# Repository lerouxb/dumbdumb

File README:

DumbDumb Terminal
===

A little smart hardware serial terminal for use with REPLs like MicroPython in the form of a Feather Wing.

Directory structure
---

### cpp

platform.io and arduino stm32-core based firmware for the stm32g071r8. Scans the keyboard matrix, handles the LCD. Reads and writes over serial. Understands a small subset of VT100 terminal functionality. Just enough to fully support MicroPython's readline REPL.

### node

Some node.js based code to parse, modify and format KiCAD's PCB file format which is some variant of LISP. Contains a script that uses all of that to modify a pcb file to layout the keyboard's buttons. A lot more convenient for making changes to the button positioning than moving each of them around manually in KiCAD's interface every time I want to make changes to the layout.

### pcb

KiCAD files for the PCB. Includes tons of custom symbols and parts.

### py

The dupterm code for the esp32 port of MicroPython to duplicate the REPL on UART 2 which is the one that's exposed by the Adafruit Huzzah32 Feather's RX and TX pins. ie. the ones that are connected to DumbDumb's STM32 microcontroller when you plug the Feather in.

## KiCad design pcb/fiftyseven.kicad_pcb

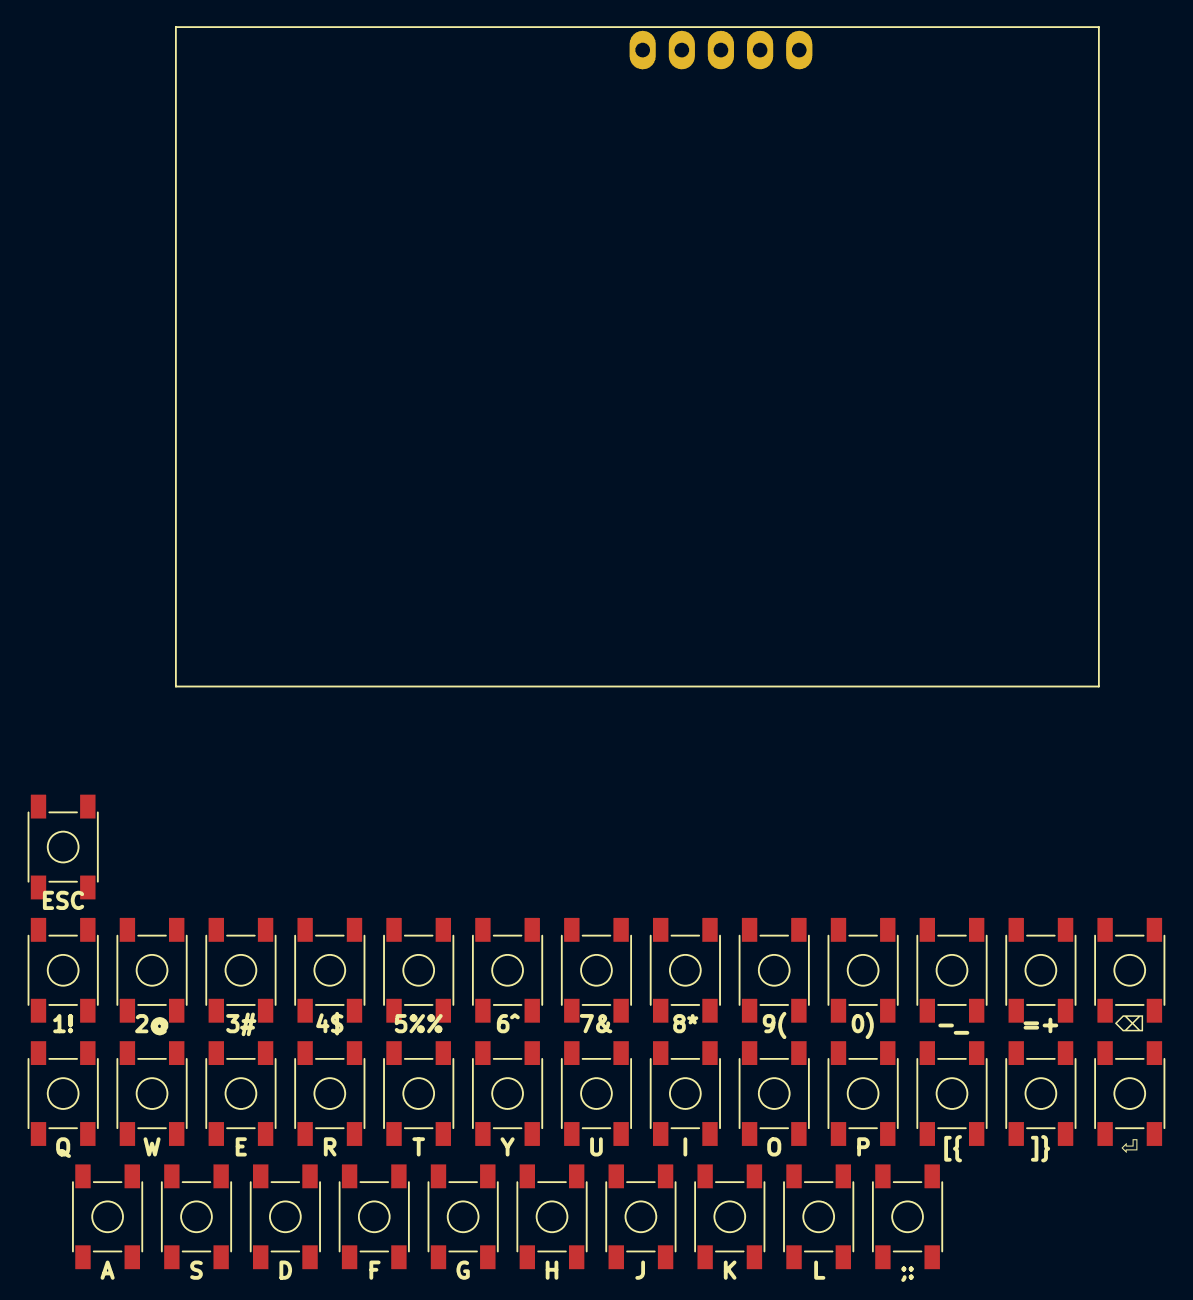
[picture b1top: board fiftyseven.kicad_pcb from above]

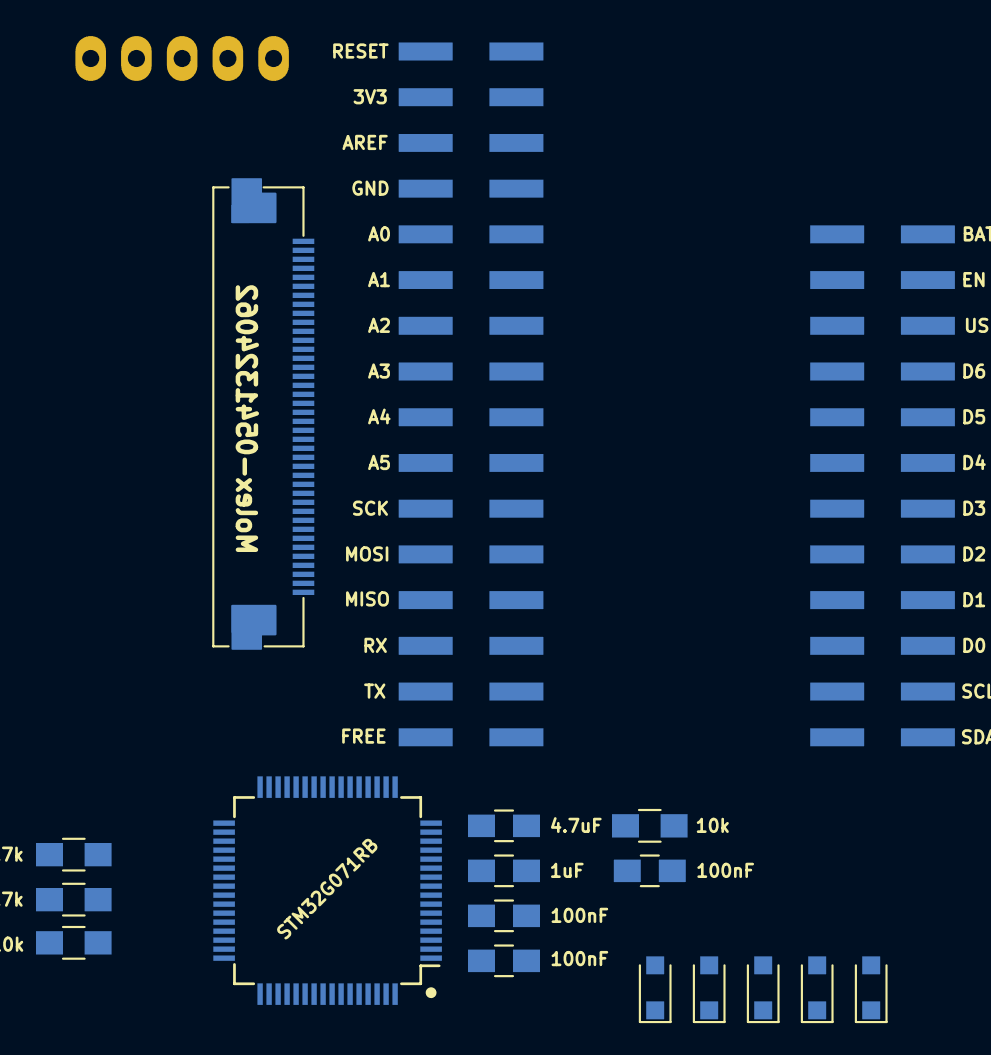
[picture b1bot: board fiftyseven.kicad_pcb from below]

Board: 2 copper layers, 56 parts (17 on the bottom side), 53 nets, no tracks yet.

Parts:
C10, C12, C17: 100nF; C_0805_HandSoldering
C11: 4.7uF; C_0805_HandSoldering
C13: 1uF; C_0805_HandSoldering
D1, D2, D3, D4, D5: D; D_SOD-323_HandSoldering
J1: Feather; FeatherHolderSMD
J2: STM32 SWD; SWD_Header
R1, R12: 10k; R_0805_HandSoldering
R10, R11: 4.7k; R_0805_HandSoldering
SW0:0, SW0:1, SW0:2, SW0:3, SW0:4, SW0:5, SW0:6, SW0:7, SW0:8, SW0:9, SW0:10, SW0:11, SW0:12, SW1:0, SW1:1, SW1:2, SW1:3, SW1:4, SW1:5, SW1:6, SW1:7, SW1:8, SW1:9, SW1:10, SW1:11, SW1:12, SW2:0, SW2:1, SW2:2, SW2:3, SW2:4, SW2:5, SW2:6, SW2:7, SW2:8, SW2:9, SW2:10: SW_Push; 4.5mm-switch
SW:ESC1: SW_Push; 4.5mm-switch
U1: STM32G071RB; STM32G0-LQFP-64
U6: 240x320_16bit; LCD-320x240

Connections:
+3V3: C10.1, C11.1, C12.1, C13.1, J1.14, J2.1, R1.1, R10.1, R11.1, SW:ESC1.1, U1.6, U1.7, U1.8
C0: SW0:0.2, SW1:0.2, SW2:0.2, U1.11
C1: SW0:1.2, SW1:1.2, SW2:1.2, U1.13
C2: SW0:2.2, SW1:2.2, SW2:2.2, U1.14
C3: SW0:3.2, SW1:3.2, SW2:3.2, U1.15
C4: SW0:4.2, SW1:4.2, SW2:4.2, U1.16
C5: SW0:5.2, SW1:5.2, SW2:5.2, U1.17
C6: SW0:6.2, SW1:6.2, SW2:6.2, U1.18
C7: SW0:7.2, SW1:7.2, SW2:7.2, U1.19
C8: SW0:8.2, SW1:8.2, SW2:8.2, U1.20
C9: SW0:9.2, SW1:9.2, SW2:9.2, U1.21
C10: SW0:10.2, SW1:10.2, U1.22
C11: SW0:11.2, SW1:11.2, U1.23
C12: SW0:12.2, SW1:12.2, U1.24
DB0: U1.27, U6.14
DB1: U1.28, U6.15
DB2: U1.29, U6.16
DB3: U1.57, U6.17
DB4: U1.58, U6.18
DB5: U1.59, U6.19
DB6: U1.60, U6.20
DB7: U1.61, U6.21
DB8: U1.62, U6.22
DB9: U1.63, U6.23
DB10: U1.30, U6.24
DB11: U1.31, U6.25
DB12: U1.32, U6.26
DB13: U1.33, U6.27
DB14: U1.34, U6.28
DB15: U1.35, U6.29
DC: U1.48, U6.11
ESC: SW:ESC1.2, U1.10
GND: C10.2, C11.2, C12.2, C13.2, C17.2, J1.16, J2.2, R12.1, U1.9, U6.1, U6.10, U6.33, U6.34, U6.35, U6.36, U6.37, U6.39
IM0: U1.36, U6.31
unnamed: D1.1, SW0:0.1, SW0:1.1, SW0:2.1, SW0:3.1, SW0:4.1, SW0:5.1, SW0:6.1, SW0:7.1, SW0:8.1, SW0:9.1, SW0:10.1, SW0:11.1, SW0:12.1
unnamed: D2.1, SW1:0.1, SW1:1.1, SW1:2.1, SW1:3.1, SW1:4.1, SW1:5.1, SW1:6.1, SW1:7.1, SW1:8.1, SW1:9.1, SW1:10.1, SW1:11.1, SW1:12.1
unnamed: D3.1, SW2:0.1, SW2:1.1, SW2:2.1, SW2:3.1, SW2:4.1, SW2:5.1, SW2:6.1, SW2:7.1, SW2:8.1, SW2:9.1
unnamed: U6.7, U6.8
R0: D1.2, U1.1
R1: D2.2, U1.2
R2: D3.2, U1.3
R3: D4.2, U1.4
R4: D5.2, U1.5
RESET: C17.1, J1.13, J2.5, R1.2, U1.12
RX: J1.26, U1.25
SCL: J1.2, R10.2, U1.37
SDA: J1.1, R11.2, U1.42
SWDCLK: J2.4, R12.2, U1.46
SWDIO: J2.3, U1.45
TX: J1.27, U1.26
~RD: U1.39, U6.13
~RES: U1.38, U6.30
~WR: U1.47, U6.12

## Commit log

2019-11-03 progress towards keyboard support
2019-11-19 textbuffer
2019-11-19 error handling
2019-11-19 rm out of date comment
2019-11-19 leave space for null terminators
2019-11-27 compile
2019-11-27 it almost works
2019-12-04 move over pcb files from fiftyseven
2019-12-04 update gitignore
2019-12-04 it works!
2019-12-26 dupterm
2019-12-26 node lib & script(s) for parsing, modifying and formatting kicad pcb lisp files
2019-12-26 Add a readme
2019-12-26 markdown
2019-12-26 photo
2019-12-26 picture of backside
2019-12-31 Add link to project
